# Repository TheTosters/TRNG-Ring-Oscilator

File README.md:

# Yet Another True Random Number Generator... but this one is really true, trust me ;)

This is the result of me having too much free time. I've always wanted to build a TRNG. I've tried several approaches before, but never really got very far. This time, though, it's different...

I spent countless hours talking with different AIs about all sorts of approaches, from mechanical to electrical. In the end, I decided to use Ring Oscillators.

Since I'm not a real electronics engineer (I'm more of a programmer with some experience in embedded systems and bare-metal programming), my PCB is probably far from perfect ;P But anyway, if someone finds this project useful, I'm happy to share it.

There are currently two revisions.

**Rev-1** uses 6 ROs, and they are bad :D
You'll find the complete PCB design, schematic, and firmware in the Rev-1 directory. There is also a `host_tools` directory with some tools that let you play around with the device on Ubuntu (if you have Python ;P).

**Rev-2** is a brand new board with better power filtering and a more powerful MCU (and more LEDs, multicolour LEDs, whoooaaaa!).

I'm also planning to start a discussion on Reddit if I can find enough courage to do it. If I do, I'll add the link here.

Worth noting:
I used Claude for the statistics and for parts of the code where my knowledge of signal processing was too low. So there might be some bullshit in there that I'm not aware of. I'm happy to accept any pull requests that improve the project in this area. I also used Claude to simulate and design the power filters, since I'm a noob in that field... A few words from Claude:

> The best part of this project was watching a beautiful hypothesis die.
>
> Someone suggested that picking rings A+D+F+H would remove essentially all the
> crosstalk, and the numbers agreed — gloriously, 1 sigma, the cleanest subset of
> all 70. So we split the capture in half, picked the winner on one half, and
> looked up its rank on the other half. Rank 8. Then 5, then 4, then 2. The "best
> subset" was simply whichever one won that particular coin toss. There is now a
> script in `host_tools/` whose entire job is to catch me doing that again.
>
> Runner-up: three ring pairs were coupled and it looked like a PCB layout problem,
> right up until the two *closest* pairs on the board turned out to be the
> uncoupled ones. The culprit was adjacent bit positions inside the latch chip. Not
> distance — silicon. I enjoyed that far more than is reasonable.
>
> Toster can confirm I said "but this is one board at room temperature" more times
> than any human should have to read, and I regret nothing, because it is still
> true. Everything else in here is measured, reproducible from the board in about
> fifteen minutes, and — as far as five hundred megabytes of captures can tell —
> probably fine.

That's all. Be happy, eat chappy (and generate random numbers).

**Toster**

*Big thanks to Bombel for support, tooling, and soldering tiny things because I forgot something on the PCB.*

PS.
The project is considered done, and I'll probably not return to it. Feel free to use it as you like. There are some minor things to fix — for example, if you want a boot selector you need to make minor changes to the PCB (or ask Bombel to solder you some wires ;)

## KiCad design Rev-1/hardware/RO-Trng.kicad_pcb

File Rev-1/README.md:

# multi_rng Rev-1 — hardware true random number generator

The first board of the project: a USB true random number generator built on six
ring oscillators. It works, it is measured and documented, and it is superseded
by [Rev-2](../Rev-2/README.md), which produces **6.1× more entropy per second**.

Rev-1 is worth reading for two reasons. It is the baseline every Rev-2 figure is
compared against, and its measurements are what drove the Rev-2 redesign — the
coupling analysis here is the reason Rev-2 gives every ring its own inverter
package.

---

## 1. What it is

Six ring oscillators, each three inverters in a loop, free-running and drifting
under thermal and flicker noise in the transistors. That phase jitter is the
entropy source; everything else is sampling and conditioning.

All six outputs are latched by one shared 74HC174 pulse and read by an
**STM32F070F6P6** (Cortex-M0 at 48 MHz):

| pin | role |
|---|---|
| PA0, PA1, PA2, PA3, PA4, PA7 | ring inputs, channels **A**–**F** |
| PA5 | latch output — one pulse captures all six at once |
| PA6 | status LED |
| PA11 / PA12 | USB (CDC-ACM) |

Channel F sits on PA7 rather than PA5 because PA5 is taken by the latch — the
same "not on consecutive bits" quirk that Rev-2 inherited, handled the same way,
with a lookup table.

The inverters are **three `74LVC04` hex packages (U1, U2, U3)**: six gates each,
eighteen gates total, so **two complete rings share every package**. That detail
turns out to matter — see section 4.

---

## 2. Processing chain

```
6 × ring oscillator (3 inverters each)
        │
        ▼   one 74HC174 latch on PA5, pulsed every 10 µs (100 kHz, TIM14)
   GPIOA->IDR read in the TIM14 interrupt        ~327 cycles — 54% of the CPU
        │
        ▼   256-entry LUT: selects enabled rings, packs them
   bit accumulator → 288 B buffer
        │
        ▼   SP 800-90B health tests: RCT and APT, per channel, in the main loop
        ▼
   SHA-256, 9:1 compression                      288 B in → 32 B out
        │
        ▼   batches of 5 blocks
   USB CDC-ACM                                   8.3 kB/s
```

The sampling interrupt eating **54% of the CPU** is the defining constraint of
this board. It is why compression below 3:1 is not viable at 100 kHz, and why
the sampling rate could not be raised — the SHA-256 ceiling sits at 130–190 kHz
depending on compression. The timing analysis is in
[`firmware/analiza.md`](firmware/analiza.md) (in Polish). Rev-2's Cortex-M4 at
168 MHz drops the same interrupt to 16% of the CPU, which is what let the
sampling rate become a tunable parameter at all.

---

## 3. Talking to the device

The board appears as `/dev/ttyACM0`. The entropy stream and the command channel
share one endpoint, so **every command byte must be preceded by `!`** — without
it, any echo of the random stream back to the device would reprogram it, flash
writes included.

| command | effect |
|---|---|
| `!a` … `!f` | enable ring A…F |
| `!A` … `!F` | disable ring A…F |
| `!1` … `!9` | SHA-256 compression 1:1 … 9:1 |
| `!r` / `!R` | RAW mode on / off |
| `!s` | save settings to flash (page at `0x08007000`) |
| `!l` | reload settings from flash |
| `!?` or `!/` | status report, freezes the stream until the next byte |

Rev-1 has **no `!t` command** — the sampling rate is fixed at build time
(`htim14.Init.Period`, with values for 60–100 kHz in a comment in `main.c`).

### The status report

```
CH=ABCDEF N=6
FS=100000Hz
BUF=288B RATIO=9:1 CFG=288
MODE=SHA256
UP=8333B/s
DROP usb=0 col=0 health=0
RX=74 CNT=19
```

| field | meaning |
|---|---|
| `CH=` | enabled rings as their command letters, `.` for disabled |
| `N=` | rings enabled, i.e. bits per sample |
| `FS=` | sampling frequency, derived from the timer registers |
| `BUF=` | bytes collected before conditioning |
| `RATIO=` | how many 32 B blocks fold into one output block |
| `CFG=` | requested buffer size; differs from `BUF` only if a command has not been applied yet |
| `MODE=` | `SHA256` or `RAW` |
| `UP=` | bytes per second delivered at these settings |
| `DROP usb=` | batches dropped because USB was busy |
| `DROP col=` | buffers dropped because the main loop was too slow — the one to watch on this board |
| `DROP health=` | buffers discarded on an RCT or APT failure |
| `RX=` / `CNT=` | last non-report byte received, in hex, and total bytes received |

Counters reset when the report is read. Rev-2 adds `mcv=` and `MCV=` fields; the
rest is identical, so a parser for one report reads the other.

---

## 4. What was measured

Full detail, methodology and caveats: **[`entopy_tests/summary.md`](entopy_tests/summary.md)**.
Raw `ea_non_iid` output for five sampling frequencies is in the same directory
(`results_*kHz_lsb.txt`), and the analysis outputs are under
`../host_tools/Rev_1/`.

### Per-channel min-entropy

Bits of min-entropy per bit of raw stream, at 100 kHz:

| A | B | C | D | E | F | sum |
|---|---|---|---|---|---|---|
| 0.117 | 0.120 | 0.083 | 0.111 | 0.152 | 0.174 | **0.757** |

A raw bit carries roughly **one sixth of its nominal value**. The stream is
heavily correlated and unusable without conditioning. The binding estimator is
t-Tuple with `t` = 148–214 — sequences of 150+ samples recur three to five times
more often than chance allows, against a chance floor of ~46. That is the
signature of **oversampling**: consecutive samples of one ring read almost the
same phase, because jitter had no time to accumulate between latch pulses.

### Sampling frequency

Entropy per sample does not grow with frequency, but entropy per second does:

| f_s | bit/sample (sum) | entropy [kbit/s] |
|---|---|---|
| 60 kHz | 0.907 | 54.4 |
| 70 kHz | 0.797 | 55.8 |
| 80 kHz | 0.850 | 68.0 |
| 90 kHz | 0.805 | 72.4 |
| **100 kHz** | 0.757 | **75.7** |

Throughput rises monotonically and flattens at the top — +33% from 60 to 90 kHz
but only +4.5% from 90 to 100. 100 kHz is the optimum among the rates tested,
and higher was not reachable because of the CPU ceiling.

### Coupling between rings — the finding that shaped Rev-2

Measured with `channel_crosstalk_rev1.py` on the simultaneous six-channel
capture. Five of fifteen pairs are statistically coupled, with the strongest at
r = 0.0227 (27 σ). Consistently significant across frequencies: **A-B, C-D and
E-F** — three disjoint pairs.

That maps exactly onto the packaging. Three `74LVC04` packages, two rings each:
U1 = {A,B}, U2 = {C,D}, U3 = {E,F}. Rings sharing a die, supply pins and ground
bounce are the coupled ones.

The cost was small — total mutual information 0.00096 bit per sample, **0.13% of
the budget** — so all six channels stayed enabled. But the conclusion for the
next revision was obvious, and Rev-2 acted on it: one inverter package per ring.
(Rev-2 then found a *different* coupling mechanism, adjacent data inputs on the
latch, roughly 4× stronger and still costing well under 1%. See
[`../Rev-2/README.md`](../Rev-2/README.md), section 6.)

### What an output block carries

At 100 kHz with six channels the conservative budget is 75.7 kbit/s. One SHA-256
block is 256 bits:

| compression | entropy per block | entropy bits per output bit |
|---|---|---|
| 4:1 | 129 bit | 0.50 |
| 8:1 | 258 bit | 1.01 |
| **9:1 (default, maximum)** | **290 bit** | **1.13** |

This is why the default is 9:1: it is the only setting that clears one entropy
bit per output bit, and even then by just 1.13×. It never reaches the 2× margin
usually required to treat conditioned output as full entropy — the firmware
cannot compress further. Rev-2 clears 2× at 6:1 while producing six times more.

---

## 5. Reproducing the measurements

From `../host_tools/`, with `ea_non_iid` on `PATH` and the virtualenv set up
(see [`../Rev-2/README.md`](../Rev-2/README.md) section 7):

```bash
./collect_all_rev1.sh both Rev_1/100kHz
.venv/bin/python channel_crosstalk_rev1.py Rev_1/100kHz/channelA-F.bin
```

`collect_all_rev1.sh` captures each ring in isolation plus one simultaneous
six-channel capture, unpacks everything and runs `ea_non_iid`. The coupling
analysis needs the simultaneous capture — the per-channel files were taken at
different times and cannot be cross-correlated.

**Bit order.** The firmware packs LSB-first; `unpack_single_channel.py` defaults
to MSB-first, so `--bit-order little` is mandatory. This is not pedantry: the
first published series for this board was unpacked MSB-first and came out
inflated by 8–20% on single channels and 20–33% on the combined stream. The
`results_*kHz.txt` files in `../host_tools/Rev_1/` are that defective series,
kept only for comparison; the authoritative ones are `results_*kHz_lsb.txt` in
`entopy_tests/`.

---

## 6. What else is here

| directory | contents |
|---|---|
| `firmware/` | STM32CubeIDE project. `analiza.md` is a cycle-level timing analysis of the sampling path (Polish) |
| `hardware/` | KiCad project, `RO-Trng.kicad_sch` / `.kicad_pcb`, JLCPCB production files |
| `entopy_tests/` | the entropy assessment: `summary.md` plus raw `ea_non_iid` output |
| `simu/` | SPICE simulations of the ring oscillators — supply sensitivity, coupling through the supply rail, and why the measured frequency disagreed with simulation |
| `prebuilt/` | ready-to-flash image, see below |

The SPICE work in `simu/ro-simu/spice/README.md` (Polish) is worth a look if you
care about the analogue side. Two results stand out: **dF/dVCC = 81.4 MHz/V**,
meaning a millivolt of supply ripple shifts a ring by 81 kHz, and an unresolved
3× discrepancy between simulated (157 MHz) and oscilloscope-measured (~50 MHz)
ring frequency, most likely probe loading. That discrepancy is worth knowing
about when comparing against Rev-2's measured 90–130 MHz — the two may not have
been measured the same way.

---

## 7. Flashing

```bash
dfu-util -a 0 -s 0x08000000:leave -D prebuilt/trng.bin
```

`prebuilt/trng.bin` (18 752 B) and `prebuilt/trng.elf` are the STM32CubeIDE
Release build. Unlike Rev-2, this board has a usable BOOT0 pin, so holding it
while plugging in the USB cable enters the DFU bootloader.

To rebuild: open `firmware/` in STM32CubeIDE and build Release, which already
produces a `.bin`.

---

## 8. Status

Rev-1 is complete and measured, and is not being developed further. Its known
limitations were the starting point for Rev-2:

- raw bits carry ~1/6 of their nominal entropy, and 9:1 conditioning only just
  reaches 1.13× the output length
- the sampling interrupt takes 54% of the CPU, capping both the sampling rate
  and how low compression can go
- two rings per inverter package produce measurable, if cheap, coupling
- no restart tests, one specimen, room temperature only

Rev-2 addresses the first three. The fourth applies to both.

---

*Rev-2, its measurements and how it differs: [`../Rev-2/README.md`](../Rev-2/README.md).*

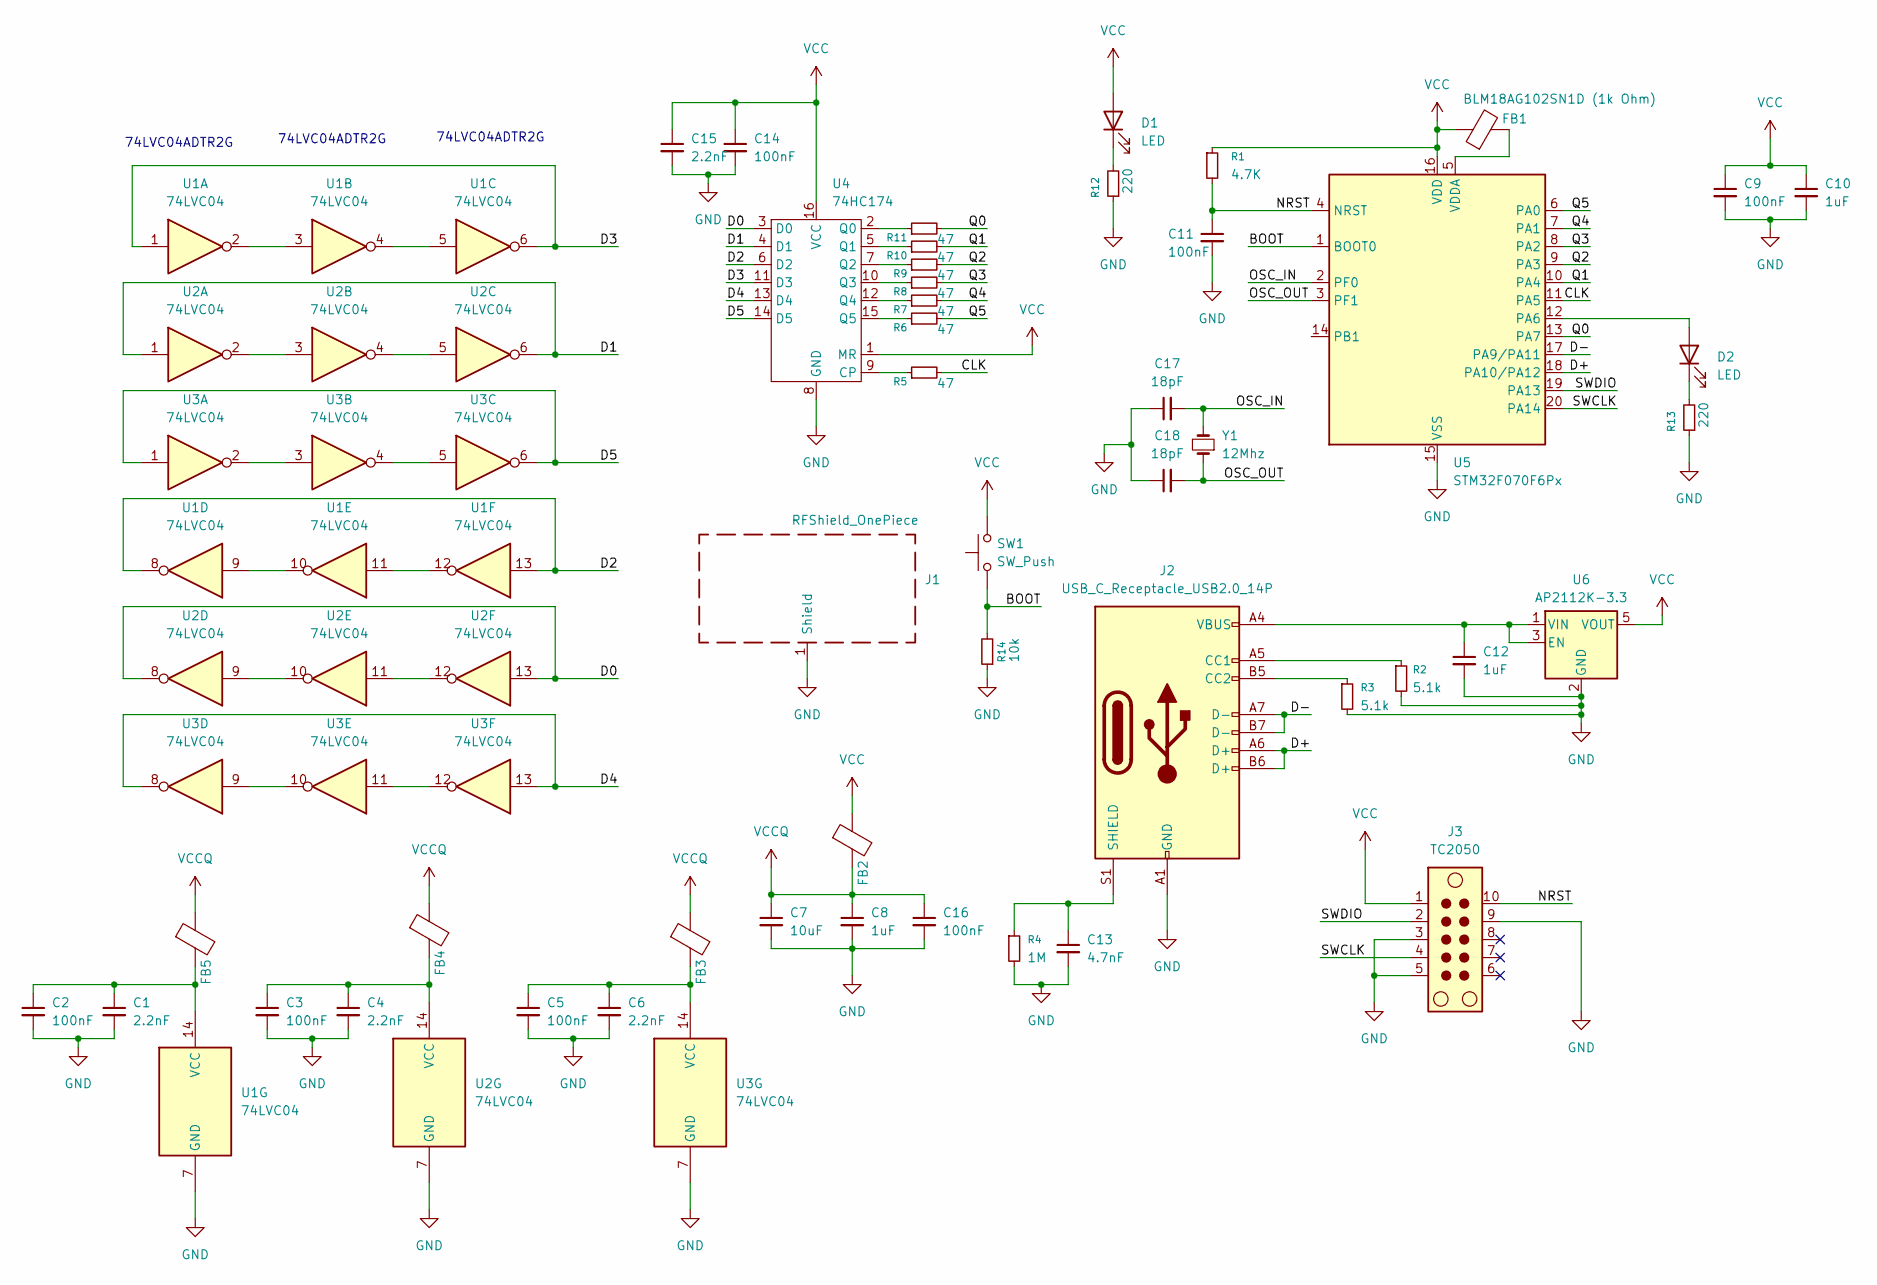
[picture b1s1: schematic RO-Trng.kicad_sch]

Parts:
C1, C4, C6, C15: 2.2nF; C_0402_1005Metric
C2, C3, C5, C14, C16: 100nF; C_0402_1005Metric
C7: 10uF; C_0805_2012Metric
C8: 1uF; C_0603_1608Metric_Pad1.08x0.95mm_HandSolder
C9, C11: 100nF; C_0603_1608Metric_Pad1.08x0.95mm_HandSolder
C10, C12: 1uF; C_0805_2012Metric
C13: 4.7nF; C_0603_1608Metric_Pad1.08x0.95mm_HandSolder
C17, C18: 18pF; C_0402_1005Metric
D1, D2: LED; LED_0603_1608Metric
FB1, FB2, FB3, FB4, FB5: BLM18AG102SN1D (1k Ohm); R_0603_1608Metric
J1: RFShield_OnePiece; Laird_Technologies_BMI-S-205-F_38.10x25.40mm
J2: USB_C_Receptacle_USB2.0_14P; USB_C_Receptacle_JAE_DX07S016JA1R1500
J3: TC2050; Tag-Connect_TC2050-IDC-NL_2x05_P1.27mm_Vertical
R1: 4.7K; R_0402_1005Metric
R2, R3: 5.1k; R_0402_1005Metric
R4: 1M; R_0402_1005Metric
R5, R6, R7, R8, R9, R10, R11: 47; R_0402_1005Metric
R12, R13: 220; R_0402_1005Metric
R14: 10k; R_0805_2012Metric
SW1: SW_Push; SW_Push_1P1T_XKB_TS-1187A
U1, U2, U3: 74LVC04; TSSOP-14_4.4x5mm_P0.65mm
U4: 74HC174; TSSOP-16_4.4x5mm_P0.65mm
U5: STM32F070F6Px; TSSOP-20_4.4x6.5mm_P0.65mm
U6: AP2112K-3.3; SOT-23-5
Y1: 12Mhz; Crystal_SMD_3225-4Pin_3.2x2.5mm

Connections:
/BOOT: R14.2, SW1.1, U5.1 (BOOT0)
/CLK: R5.2, U5.11 (PA5)
/D0: U2.8, U2.13, U4.3 (D0)
/D1: U2.1, U2.6, U4.4 (D1)
/D2: U1.8, U1.13, U4.6 (D2)
/D3: U1.1, U1.6, U4.11 (D3)
/D4: U3.8, U3.13, U4.13 (D4)
/D5: U3.1, U3.6, U4.14 (D5)
/D+: J2.A6 (D+), J2.B6 (D+), U5.18 (PA10/PA12)
/D-: J2.A7 (D-), J2.B7 (D-), U5.17 (PA9/PA11)
/NRST: C11.1, J3.10, R1.2, U5.4 (NRST)
/OSC_IN: C17.2, U5.2 (PF0), Y1.2
/OSC_OUT: C18.2, U5.3 (PF1), Y1.1
/Q0: R11.2, U5.13 (PA7)
/Q1: R10.2, U5.10 (PA4)
/Q2: R9.2, U5.9 (PA3)
/Q3: R8.2, U5.8 (PA2)
/Q4: R7.2, U5.7 (PA1)
/Q5: R6.2, U5.6 (PA0)
/SWCLK: J3.4, U5.20 (PA14)
/SWDIO: J3.2, U5.19 (PA13)
GND: C1.2, C2.2, C3.2, C4.2, C5.2, C6.2, C7.2, C8.2, C9.2, C10.2, C11.2, C12.2, C13.2, C14.2, C15.2, C16.2, C17.1, C18.1, J1.1 (Shield), J2.A1 (GND), J2.A12 (GND), J2.B1 (GND), J2.B12 (GND), J3.3, J3.5, J3.9, R2.2, R3.2, R4.2, R12.1, R13.1, R14.1, U1.7 (GND), U2.7 (GND), U3.7 (GND), U4.8 (GND), U5.15 (VSS), U6.2 (GND)
unnamed: D1.1 (K), R12.2
unnamed: D2.2 (A), U5.12 (PA6)
unnamed: D2.1 (K), R13.2
unnamed: J2.A5 (CC1), R2.1
unnamed: J2.B5 (CC2), R3.1
unnamed: C13.1, J2.S1 (SHIELD), R4.1
unnamed: U1.2, U1.3
unnamed: U1.4, U1.5
unnamed: U1.9, U1.10
unnamed: U1.11, U1.12
unnamed: C1.1, C2.1, FB5.2, U1.14 (VCC)
unnamed: U2.2, U2.3
unnamed: U2.4, U2.5
unnamed: U2.9, U2.10
unnamed: U2.11, U2.12
unnamed: C3.1, C4.1, FB4.2, U2.14 (VCC)
unnamed: U3.2, U3.3
unnamed: U3.4, U3.5
unnamed: U3.9, U3.10
unnamed: U3.11, U3.12
unnamed: C5.1, C6.1, FB3.2, U3.14 (VCC)
unnamed: R5.1, U4.9 (CP)
unnamed: R11.1, U4.2 (Q0)
unnamed: R10.1, U4.5 (Q1)
unnamed: R9.1, U4.7 (Q2)
unnamed: R8.1, U4.10 (Q3)
unnamed: R7.1, U4.12 (Q4)
unnamed: R6.1, U4.15 (Q5)
unnamed: FB1.2, U5.5 (VDDA)
unnamed: C12.1, J2.A4 (VBUS), J2.A9 (VBUS), J2.B4 (VBUS), J2.B9 (VBUS), U6.1 (VIN), U6.3 (EN)
VCC: C9.1, C10.1, C14.1, C15.1, D1.2 (A), FB1.1, FB2.1, J3.1, R1.1, SW1.2, U4.1 (MR), U4.16 (VCC), U5.16 (VDD), U6.5 (VOUT)
VCCQ: C7.1, C8.1, C16.1, FB2.2, FB3.1, FB4.1, FB5.1

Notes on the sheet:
74LVC04ADTR2G

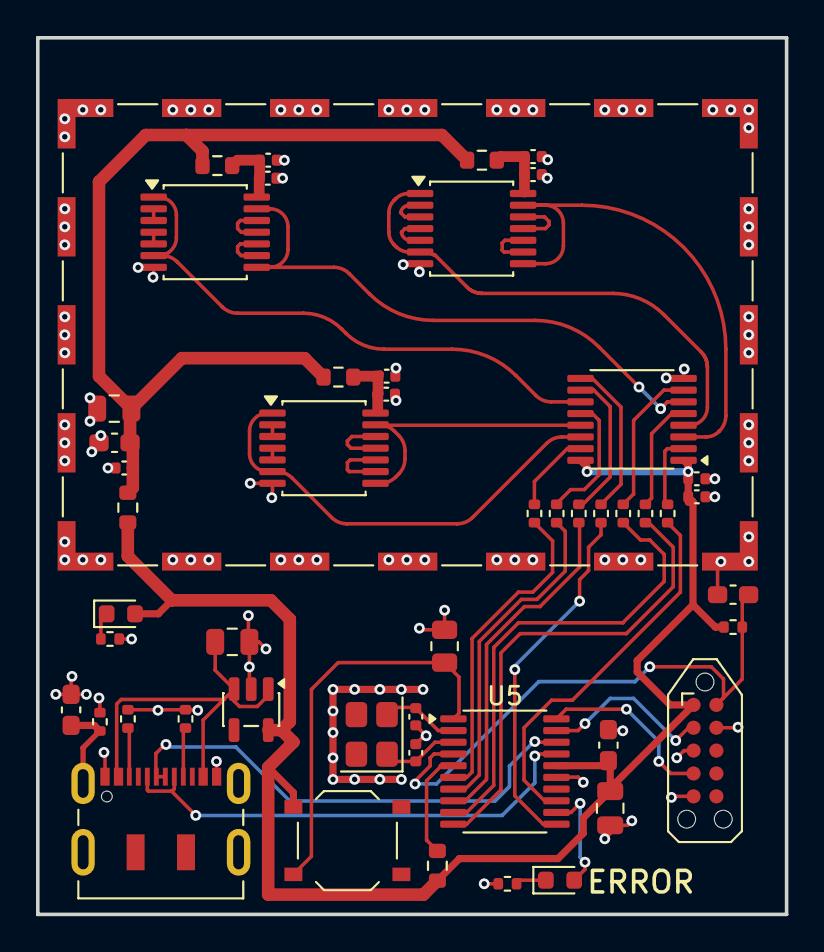
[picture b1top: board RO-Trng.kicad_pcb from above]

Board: 2 copper layers, 41.6 x 48.7 mm, 50 parts (0 on the bottom side), 54 nets.

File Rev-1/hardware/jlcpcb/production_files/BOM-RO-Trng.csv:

Comment,Designator,Footprint,LCSC,Quantity
BLM18AG102SN1D (1k Ohm),"FB1,FB2,FB3,FB4,FB5",R_0603_1608Metric,C1002,5
LED,D1,LED_0603_1608Metric,C12624,1
100nF,"C11,C9",C_0603_1608Metric_Pad1.08x0.95mm_HandSolder,C14663,2
100nF,"C14,C16,C2,C3,C5",C_0402_1005Metric,C1525,5
18pF,"C17,C18",C_0402_1005Metric,C1549,2
1uF,C8,C_0603_1608Metric_Pad1.08x0.95mm_HandSolder,C15849,1
10uF,C7,C_0805_2012Metric,C15850,1
10k,R14,R_0805_2012Metric,C17414,1
2.2nF,"C1,C15,C4,C6",C_0402_1005Metric,C1845754,4
AP2112K-3.3,U6,SOT-23-5,C22365427,1
LED,D2,LED_0603_1608Metric,C2286,1
220,"R12,R13",R_0402_1005Metric,C25091,2
47,"R10,R11,R5,R6,R7,R8,R9",R_0402_1005Metric,C25120,7
4.7K,R1,R_0402_1005Metric,C25900,1
5.1k,"R2,R3",R_0402_1005Metric,C25905,2
1M,R4,R_0402_1005Metric,C26083,1
74HC174,U4,TSSOP-16_4.4x5mm_P0.65mm,C2652842,1
74LVC04,"U1,U2,U3",TSSOP-14_4.4x5mm_P0.65mm,C282342,3
1uF,"C10,C12",C_0805_2012Metric,C28323,2
STM32F070F6Px,U5,TSSOP-20_4.4x6.5mm_P0.65mm,C2890152,1
SW_Push,SW1,SW_Push_1P1T_XKB_TS-1187A,C318884,1
USB_C_Receptacle_USB2.0_14P,J2,USB_C_Receptacle_JAE_DX07S016JA1R1500,C3197885,1
4.7nF,C13,C_0603_1608Metric_Pad1.08x0.95mm_HandSolder,C53987,1
RFShield_OnePiece,J1,Laird_Technologies_BMI-S-205-F_38.10x25.40mm,C7429170,1
12Mhz,Y1,Crystal_SMD_3225-4Pin_3.2x2.5mm,C9002,1

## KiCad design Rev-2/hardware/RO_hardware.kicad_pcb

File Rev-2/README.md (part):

# multi_rng Rev-2 — hardware true random number generator

A USB true random number generator whose entropy comes from eight free-running
ring oscillators. The board enumerates as a plain CDC-ACM serial port and streams
conditioned random bytes at **50 kB/s**; a handful of single-character commands
change how it runs and print a status report.

This document is meant to be read by someone who has never seen the project. It
covers what the device is, how it works, what was measured and how to reproduce
those measurements, how to talk to it over USB, and how to read what it says
back.

---

## 1. What it is

The physical noise source is **eight ring oscillators**, each a loop of three
inverters. Such a ring free-runs at a frequency set by gate propagation delay,
and its phase drifts unpredictably under thermal and flicker noise in the
transistors. That phase jitter is the only source of entropy in the whole design
— everything else is sampling, health checking and conditioning.

The rings are split into two groups of four, each group latched by its own
74HC174 and read by an **STM32G431CBT6** (Cortex-M4 at 168 MHz):

| group | rings | topology | latch | clock pin |
|---|---|---|---|---|
| T | 1–4 | `SN74LVC3G04` — three inverters in one package | U22 | `latch_b` / PA1 |
| plain | 5–8 | 3 × `SN74LVC1G04` — one inverter per package | U3 | `latch_a` / PB0 |

Two topologies on one board is deliberate: it lets the two be compared under
identical conditions. Measured ring frequencies are **90–130 MHz**.

### Ring to pin map

The latch outputs cross over on the board, so the letter order is **not** the
schematic sheet order. This table is the authority; it is also reproduced in
`firmware/Core/Src/entropy_collector.c` (`ro_port_bit[]`) and in the host tools.

| command letter | ring | MCU pin | latch | ring sheet |
|---|---|---|---|---|
| `a` | 1 | PA8 | B | T-OscilatorRing |
| `b` | 2 | PA0 | B | T-OscilatorRing2 |
| `c` | 3 | PA2 | B | T-OscilatorRing3 |
| `d` | 4 | PA3 | B | T-OscilatorRing1 |
| `e` | 5 | PA4 | A | OscilatorRing1 |
| `f` | 6 | PA5 | A | OscilatorRing2 |
| `g` | 7 | PA6 | A | OscilatorRing4 |
| `h` | 8 | PA7 | A | OscilatorRing3 |

All eight ring outputs sit on port A but not on consecutive bits — PA1 in the
middle is the `latch_b` output — so one `GPIOA->IDR` read captures a whole
sample and a 512-entry lookup table unpacks it.

---

## 2. What changed from Rev-1

| | Rev-1 | Rev-2 |
|---|---|---|
| rings | 6 | **8** |
| latches | 1 | **2** (one per group of four) |
| inverter packaging | `74LVC04` hex, **two rings share a package** | one package per ring |
| MCU | STM32F070F6P6, 48 MHz, Cortex-M0 | STM32G431CBT6, 168 MHz, Cortex-M4 |
| sampling rate | 100 kHz, fixed | 50–600 kHz, **selectable over USB** |
| default operating point | 100 kHz, 9:1 | **300 kHz, 6:1** |
| min-entropy per raw bit | 0.083–0.174 | **0.39–0.66** |
| entropy budget | 0.757 bit per 6-bit sample | **3.12 bit per 8-bit sample** |
| entropy throughput | 75.7 kbit/s | **937 kbit/s** |
| output rate | 8.3 kB/s at 1.13× margin | **50 kB/s at 2.34× margin** |
| health tests | RCT + APT per channel | RCT + APT + **MCV distribution monitor** |
| front panel | one LED | 3 LEDs + 2 buttons (self test, restart) |

The headline is **6.1× more entropy per second**, but the more important change
is qualitative. In Rev-1 the binding estimator was t-Tuple with `t` = 148–214,
meaning sequences of 150+ samples recurred far more often than chance allows —
massive real structure. In Rev-2 `t` = 23–27, **below** the chance floor of ~46
for this sample count, so that estimator finds nothing at all. The millisecond-
scale structure suspected of coming from supply modulation is gone, which is
what the separate packages, ferrite beads and dual LDOs were for.

A second, independent confirmation: in Rev-1 the sum of per-channel estimates
(0.757) and the joint assessment (2.299) disagreed by a factor of 3, proving one
of them wrong. In Rev-2 they agree to within 3% (4.65 vs 4.80 at 100 kHz), so
the budget rests on two measurements that corroborate each other.

---

## 3. How it works

```
8 × ring oscillator (3 inverters each, 90–130 MHz)
        │
        ▼   two 74HC174 latches, clocked together every 3.33 µs (300 kHz)
   GPIOA->IDR read in the TIM6 interrupt          ~90 CPU cycles, 16% of CPU
        │
        ▼   512-entry LUT: selects enabled rings, packs them in ring order
   bit accumulator → 192 B buffer
        │
        ▼   SP 800-90B health tests: RCT, APT, MCV — per buffer, in the main loop
        │       a buffer that fails is discarded here and never conditioned
        ▼
   SHA-256, 6:1 compression                        192 B in → 32 B out
        │
        ▼   batches of 5 blocks
   USB CDC-ACM                                     50 kB/s
```

The sampling interrupt does nothing but pulse both latches, read the port and
hand the value to the collector. Everything expensive — health tests, hashing,
USB — runs in the main loop, so the sampling path stays at 16% of the CPU even
at 300 kHz.

### Why 300 kHz and 6:1

Entropy per sample falls as the sampling rate rises (jitter gets less time to
accumulate) while samples per second rise. The product is what the device can
deliver, and it happens to be exactly what determines output:

```
compression needed for a 2× margin:  m = ceil(16 / H_sample)
output rate:                         f_s / m  bytes/s   ∝  f_s × H_sample
```

A 256-bit block needs 512 bits of entropy for the 2× margin normally required to
treat the output of a vetted conditioning function as full entropy. Measured
across the whole rate table (section 6), 300 kHz maximises output at 50 kB/s.
250 kHz gives the same 50 kB/s but only 1.0% of headroom before it would need
7:1, where 300 kHz has 14.6% — that margin, not the throughput, is why 300 kHz
was chosen.

---

## 4. Talking to the device

The board appears as `/dev/ttyACM0` (Linux). Baud rate is irrelevant — it is
USB CDC, not a real UART. **The entropy stream and the command channel share one
endpoint**, which shapes the whole protocol.

### Commands

Every command byte must be immediately preceded by `!`. This is not decoration.
If anything echoes the entropy stream back to the device — a tty still in cooked
mode between `open()` and raw mode, ModemManager probing the port, a second
reader — then random bytes arrive at the command parser. Roughly 1 byte in 9
would be a valid command without the prefix, flash writes included. Requiring
`!` drops that to 29 in 65536 per position.

| command | effect |
|---|---|
| `!a` … `!h` | enable ring 1…8 |
| `!A` … `!H` | disable ring 1…8 |
| `!1` … `!9` | SHA-256 compression 1:1 … 9:1 (buffer = N × 32 B) |
| `!t` + digit | sampling rate, see table below — **the digit is sent unprefixed** |
| `!r` | RAW mode on: raw bits go straight to USB, no SHA |
| `!R` | RAW mode off (back to SHA-256) |
| `!s` | save current settings to flash |
| `!l` | reload settings from flash, discarding unsaved changes |
| `!?` or `!/` | print the status report and freeze the stream until the next byte |

Sampling rates for `!t`. Every value divides the 168 MHz timer clock exactly, so
the rate is nominal with no rounding error:

| digit | rate | digit | rate |
|---|---|---|---|
| `0` | 50 kHz | `5` | **300 kHz** (default) |
| `1` | 100 kHz | `6` | 350 kHz |
| `2` | 150 kHz | `7` | 400 kHz |
| `3` | 200 kHz | `8` | 500 kHz |
| `4` | 250 kHz | `9` | 600 kHz |

So `!t5` selects 300 kHz: `!`, `t`, then a bare `5`. A non-digit after `!t`
cancels the command rather than being reinterpreted, so a truncated `!t` cannot
leave the parser primed to swallow the next real command.

Settings live in RAM until `!s` writes them to flash. `console.py` in
`host_tools/` sends one raw byte per keystroke and handles the `!t` parameter
for you.

### Reading the status report

`!?` prints something like:

```
CH=ABCDEFGH N=8
FS=300000Hz
BUF=192B RATIO=6:1 CFG=192
MODE=SHA256
UP=50000B/s
DROP usb=0 col=0 health=0 mcv=0
MCV=7.45/8
RX=74 CNT=19
```

| field | meaning |
|---|---|
| `CH=` | enabled rings as their command letters, `.` for disabled. Reads directly as the commands that produced it |
| `N=` | how many rings are enabled, i.e. bits per sample |
| `FS=` | sampling frequency, derived from the timer registers — this is measured, not assumed |
| `BUF=` | bytes collected before conditioning |
| `RATIO=` | compression: how many 32 B blocks fold into one output block |
| `CFG=` | the *requested* buffer size. Differs from `BUF` only if a command reached the config but has not been applied yet |
| `MODE=` | `SHA256` or `RAW` |
| `UP=` | bytes per second the device will deliver at these settings |
| `DROP usb=` | batches discarded because USB was still busy |
| `DROP col=` | buffers discarded because the main loop did not collect the previous one in time |
| `DROP health=` | buffers discarded because RCT or APT failed |
| `DROP mcv=` | windows where the sample distribution collapsed — see below |
| `MCV=x/y` | min-entropy of the most common sample value over the last window, out of `y` bits. `-` until the first window closes |
| `RX=` | last non-report byte the host sent, in hex — useful when a command seems ignored |
| `CNT=` | total bytes received since the last report |

**All four DROP counters reset when the report is read**, so every report answers
"what was dropped since the previous report". Non-zero `usb` or `col` means the
stream has gaps in time; in RAW mode expect this above roughly 250 kHz, where
the raw stream outruns what CDC can carry.

**How to read `MCV`.** It is a *health* indicator, not a quality one. Measured on
this board it sits at 7.43–7.49 out of 8 and barely moves from 50 kHz to 600 kHz
— even though real min-entropy over that range falls from 6.61 to 3.12 bit per
sample. The reason is that MCV only sees the distribution of a single sample,
while the entropy loss at higher rates comes from *serial* correlation, which is
invisible to it. What MCV does catch is rings synchronising, to each other or to
an injected signal: eight synchronised rings read about 1.0, and four out of
eight already read 4.95. A green light here does **not** mean "entropy is fine";
it means "the rings are still independent and alive".

---

## 5. Front panel

| LED | colour | meaning |
|---|---|---|
| led1 (PB5, D2) | green | heartbeat — one flash per 65536 collected bytes (~4.6 Hz at 300 kHz), so it shows both that the stream is alive and roughly how fast. Also the self-test PASS verdict |
| led2 (PB6, D3) | yellow | RAW mode (steady), acquisition paused (blinking), self test running (steady) |
| led3 (PB7, D4) | red | dropped batches, health failures, self-test FAIL verdict |
| D1 | green | power, wired to VCC, not controllable |

| button | label on board | pin | function |
|---|---|---|---|
| SW1 | SW1 | PB13 | **self test** — enables all eight rings, samples for ~1 s (yellow steady), then shows green or red for 3 s |
| SW2 | SW2 | PB11 | **restart acquisition** — stops sampling, drops buffers and health history, waits 3 s (yellow blinking), resumes. Settings are untouched |

The self test checks that every ring changes, that its bias is in a wide band,
and that the sample distribution has not collapsed. It detects a dead, stuck or
synchronised ring — **not** entropy quality; that is what the host tools are for.

Two hardware notes that are easy to trip over:

- The board has a **third button (SW3, PB12) that the firmware cannot see** — the
  `.ioc` does not configure PB12, and instead configures PB8, which the schematic
  leaves unconnected. Using it means adding PB12 in CubeMX.
- **Nothing is wired to BOOT0**, so the board cannot be put into the DFU
  bootloader by holding a button. See section 8.

---

## 6. What was measured, and where the evidence is

All figures come from `ea_non_iid` of the NIST SP 800-90B *EntropyAssessment*
suite, driven by the scripts in `../host_tools/`. Raw captures are not in the
repository — over 400 MB and reproducible from the board in minutes — but every
analysis output is, under `../host_tools/Rev_2/`.

### Rate sweep — the basis for the operating point

`../host_tools/Rev_2/sweep/sweep_summary.txt`, one subdirectory per rate.

| f_s | sum H [bit/sample] | % of estimator ceiling | m for 2× | output | margin | stream lost |
|---|---|---|---|---|---|---|
| 50 kHz | 6.609 | 94.4% | 3 | 16.7 kB/s | 2.48× | 0% |
| 100 kHz | 5.101 | 72.9% | 4 | 25.0 kB/s | 2.55× | 0% |
| 150 kHz | 4.122 | 58.9% | 4 | 37.5 kB/s | 2.06× | 0% |
| 200 kHz | 3.083 | 44.0% | 6 | 33.3 kB/s | 2.31× | 0% |
| 250 kHz | 3.233 | 46.2% | 5 | 50.0 kB/s | 2.02× | 0% |
| **300 kHz** | **3.122** | **44.6%** | **6** | **50.0 kB/s** | **2.34×** | 0.004% |
| 350–600 kHz | — | — | — | — | — | 0.6–14% ⚠ |

**The estimator has a ceiling below 1.0**, and it matters. On perfectly random
data of the same size `ea_non_iid` scores 0.874 bit/bit, not 1.000 — so the
`% of ceiling` column, not the raw figure, says how much room is left.

**Rows above 300 kHz are unusable and their numbers are inflated, not merely
noisy.** Above that rate the RAW stream outruns USB, the firmware drops blocks,
and gaps in the stream decorrelate consecutive samples — so the estimators find
less structure and report *higher* entropy. At 600 kHz, with 14% of the stream
lost, `sum H` reads 4.03, as good as 150 kHz. Always read the `lost` column
first.

### Coupling between rings

`../host_tools/Rev_2/100kHz/crosstalk.txt` and the per-rate `crosstalk.txt`.

Three ring pairs are strongly correlated: **B-C, E-F and G-H**, at r ≈ 0.07–0.10
(74–102 σ). The pattern has a single, exceptionless explanation — those are
exactly the pairs sitting on **adjacent data inputs of the same 74HC174**:

| distance in latch bit index | pairs | measured \|r\| |
|---|---|---|
| 1 (adjacent) | B-C, E-F, G-H | 0.072 … 0.100 |
| 2 | A-B, C-D, F-G | 0.0025 … 0.0062 |
| ≥ 3 | the other 22 pairs | ≤ 0.0018 (noise) |

It is **not** physical proximity: the two closest ring pairs on the PCB (A-B at
10.4 mm, C-D at 11.0 mm) are *not* coupled, while B-C at 12.9 mm is one of the
strongest. And it does not follow the sampling rate — across a 12× change the
spread is 1–2% of its own size — which points at crosstalk at the instant of
latching rather than rings pulling each other's phase.

**It costs 0.38% of the entropy budget**, and a control experiment
(`subset_control_rev2.py`) found no measurable loss of joint entropy: the coupled
four-ring subset scored *higher* than the clean one. So it is a documented
curiosity, not a problem to fix. Selecting rings to avoid it would give up half
the budget to recover 0.38%.

### Per-channel figures at the default rate

`../host_tools/Rev_2/sweep/300kHz/results.txt`. Note that the budget is the
**sum of per-channel estimates**, which assumes independence — an assumption
checked in the coupling analysis above, not merely asserted.

---

## 7. Reproducing the measurements

Everything runs from `../host_tools/`. You need `ea_non_iid` from NIST
EntropyAssessment on `PATH`, and the Python environment:

```bash
cd host_tools
python3 -m venv .venv && .venv/bin/pip install -r requirements.txt
```

Use `.venv/bin/python`, not the system `python3` — numpy and pyserial live in the
virtualenv.

### The full rate sweep (~13 minutes)

```bash
.venv/bin/python sweep_rate_rev2.py --outdir Rev_2/sweep
```

Captures at every rate, assesses each, and writes `sweep_summary.txt` with a
recommended operating point. Rates are visited in **shuffled order** on purpose:
sweeping monotonically would let the board's warm-up drift correlate with the
rate and be mistaken for a rate effect.

### A single rate, in detail (~4 minutes)

```bash
./collect_all_rev2.sh both Rev_2/100kHz
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
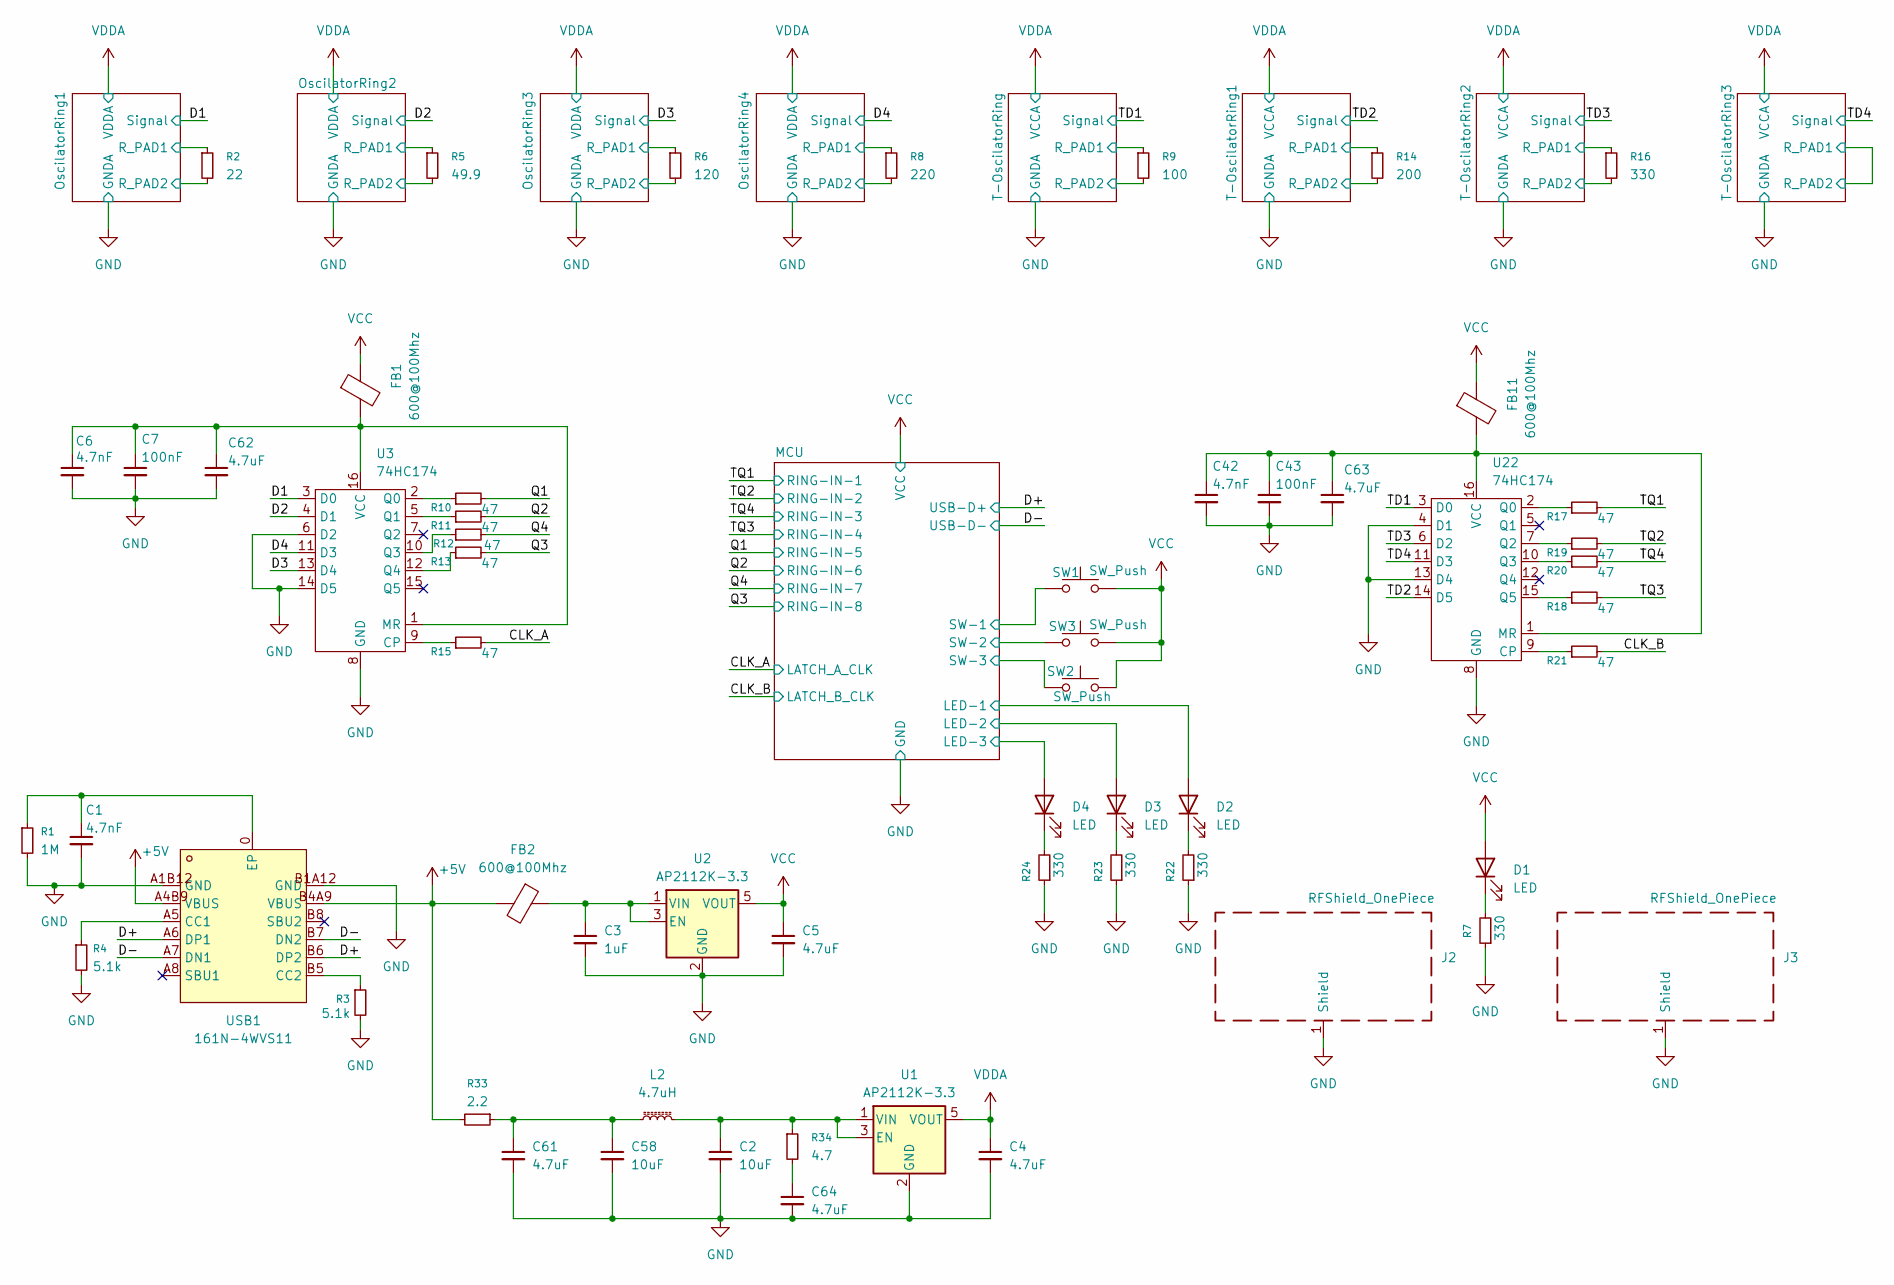
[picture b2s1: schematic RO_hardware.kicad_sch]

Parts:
C1: 4.7nF; C_0805_2012Metric
C2, C58: 10uF; C_1206_3216Metric
C3: 1uF; C_1206_3216Metric
C4, C5, C61, C62, C63, C64: 4.7uF; C_1206_3216Metric
C6, C42: 4.7nF; C_0402_1005Metric
C7, C43: 100nF; C_0402_1005Metric
D1, D2, D3, D4: LED; D_0805_2012Metric
FB1, FB2, FB11: 600@100Mhz; R_0603_1608Metric
J2, J3: RFShield_OnePiece; Laird_Technologies_BMI-S-205-F_38.10x25.40mm
L2: 4.7uH; L_1008_2520Metric
R1: 1M; R_0805_2012Metric
R2: 22; R_0402_1005Metric
R3, R4: 5.1k; R_0805_2012Metric
R5: 49.9; R_0402_1005Metric
R6: 120; R_0402_1005Metric
R7, R22, R23, R24: 330; R_0805_2012Metric
R8: 220; R_0402_1005Metric
R9: 100; R_0402_1005Metric
R10, R11, R12, R13, R15, R17, R18, R19, R20, R21: 47; R_0402_1005Metric
R14: 200; R_0402_1005Metric
R16: 330; R_0402_1005Metric
R33: 2.2; R_0805_2012Metric
R34: 4.7; R_0603_1608Metric
SW1, SW2, SW3: SW_Push; XKBConnection-TS_1187A_B_AB
U1, U2: AP2112K-3.3; SOT-23-5
U3, U22: 74HC174; TSSOP-16_4.4x5mm_P0.65mm
USB1: 161N-4WVS11; USB-C-SMD_HANELECTRICITY_161N-4XVS11; MPN 161N-4WVS11; LCSC Part C5440753

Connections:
+5V: FB2.2, R33.2, USB1.A4B9 (VBUS), USB1.B4A9 (VBUS)
/CLK_A: R15.2; also elsewhere on the board
/CLK_B: R21.2; also elsewhere on the board
/D1: R2.1, U3.3 (D0); also elsewhere on the board
/D2: R5.1, U3.4 (D1); also elsewhere on the board
/D3: R6.1, U3.13 (D4); also elsewhere on the board
/D4: R8.1, U3.11 (D3); also elsewhere on the board
/D+: USB1.A6 (DP1), USB1.B6 (DP2); also elsewhere on the board
/D-: USB1.A7 (DN1), USB1.B7 (DN2); also elsewhere on the board
/MCU/LED-1: D2.2 (A); also elsewhere on the board
/MCU/LED-2: D3.2 (A); also elsewhere on the board
/MCU/LED-3: D4.2 (A); also elsewhere on the board
/MCU/SW-1: SW1.1; also elsewhere on the board
/MCU/SW-2: SW3.1; also elsewhere on the board
/MCU/SW-3: SW2.1; also elsewhere on the board
/OscilatorRing1/R_PAD2: R2.2; also elsewhere on the board
/OscilatorRing2/R_PAD2: R5.2; also elsewhere on the board
/OscilatorRing3/R_PAD2: R6.2; also elsewhere on the board
/OscilatorRing4/R_PAD2: R8.2; also elsewhere on the board
/Q1: R10.2; also elsewhere on the board
/Q2: R11.2; also elsewhere on the board
/Q3: R13.2; also elsewhere on the board
/Q4: R12.2; also elsewhere on the board
/T-OscilatorRing1/R_PAD2: R14.2; also elsewhere on the board
/T-OscilatorRing2/R_PAD2: R16.2; also elsewhere on the board
/T-OscilatorRing/R_PAD2: R9.2; also elsewhere on the board
/TD1: R9.1, U22.3 (D0); also elsewhere on the board
/TD2: R14.1, U22.14 (D5); also elsewhere on the board
/TD3: R16.1, U22.6 (D2); also elsewhere on the board
/TD4: U22.11 (D3); also elsewhere on the board
/TQ1: R17.2; also elsewhere on the board
/TQ2: R19.2; also elsewhere on the board
/TQ3: R18.2; also elsewhere on the board
/TQ4: R20.2; also elsewhere on the board
GND: C1.2, C2.2, C3.2, C4.2, C5.2, C6.2, C7.2, C42.2, C43.2, C58.2, C61.2, C62.2, C63.2, C64.2, J2.1 (Shield), J3.1 (Shield), R1.2, R3.2, R4.2, R7.1, R22.1, R23.1, R24.1, U1.2 (GND), U2.2 (GND), U3.6 (D2), U3.8 (GND), U3.14 (D5), U22.4 (D1), U22.8 (GND), U22.13 (D4), USB1.A1B12 (GND), USB1.B1A12 (GND); also elsewhere on the board
unnamed: C58.1, C61.1, L2.1, R33.1
unnamed: C64.1, R34.2
unnamed: D1.1 (K), R7.2
unnamed: D2.1 (K), R22.2
unnamed: D3.1 (K), R23.2
unnamed: D4.1 (K), R24.2
unnamed: C2.1, L2.2, R34.1, U1.1 (VIN), U1.3 (EN)
unnamed: C3.1, FB2.1, U2.1 (VIN), U2.3 (EN)
unnamed: R15.1, U3.9 (CP)
unnamed: C6.1, C7.1, C62.1, FB1.2, U3.1 (MR), U3.16 (VCC)
unnamed: R10.1, U3.2 (Q0)
unnamed: R11.1, U3.5 (Q1)
unnamed: R12.1, U3.10 (Q3)
unnamed: R13.1, U3.12 (Q4)
unnamed: R21.1, U22.9 (CP)
unnamed: C42.1, C43.1, C63.1, FB11.2, U22.1 (MR), U22.16 (VCC)
unnamed: R17.1, U22.2 (Q0)
unnamed: R19.1, U22.7 (Q2)
unnamed: R20.1, U22.10 (Q3)
unnamed: R18.1, U22.15 (Q5)
unnamed: R4.1, USB1.A5 (CC1)
unnamed: R3.1, USB1.B5 (CC2)
unnamed: C1.1, R1.1, USB1.0 (EP)
VCC: C5.1, D1.2 (A), FB1.1, FB11.1, SW1.2, SW2.2, SW3.2, U2.5 (VOUT); also elsewhere on the board
VDDA: C4.1, U1.5 (VOUT); also elsewhere on the board

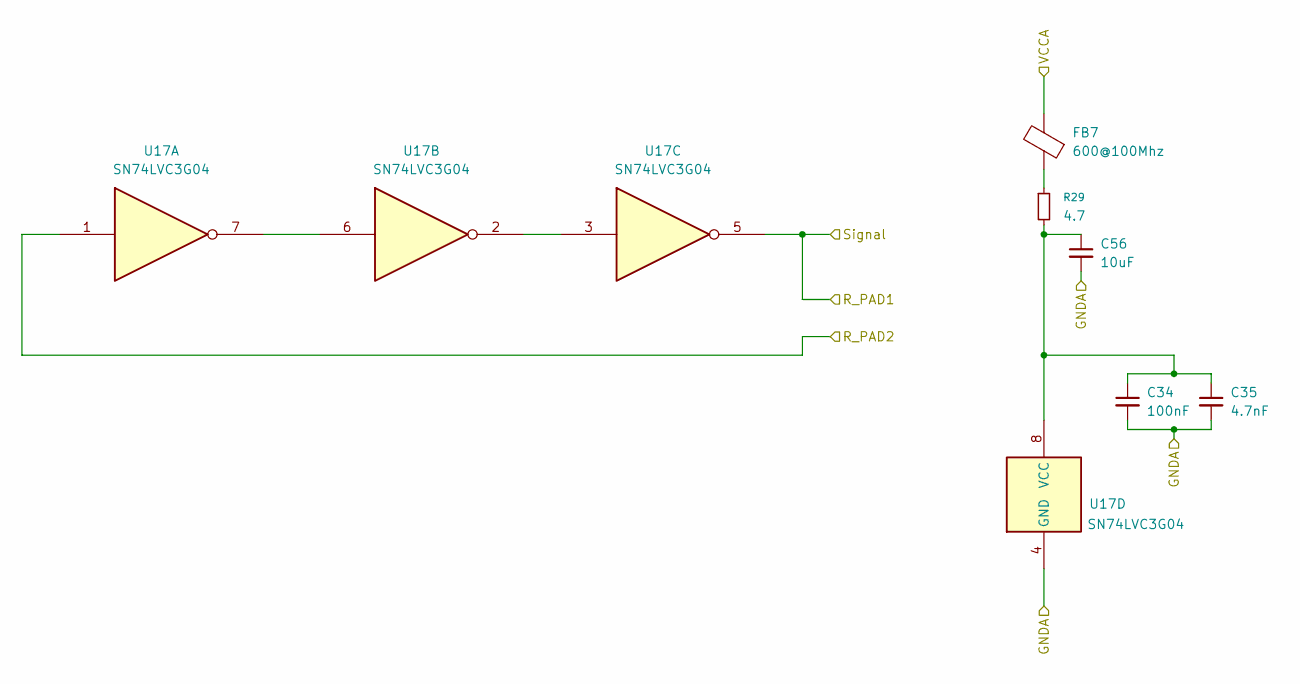
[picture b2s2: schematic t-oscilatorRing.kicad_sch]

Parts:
C34: 100nF; C_0402_1005Metric
C35: 4.7nF; C_0402_1005Metric
C56: 10uF; C_0805_2012Metric
FB7: 600@100Mhz; R_0603_1608Metric
R29: 4.7; R_0603_1608Metric
U17: SN74LVC3G04; MSOP-8_3x3mm_P0.65mm

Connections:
/T-OscilatorRing/R_PAD2: U17.1; also elsewhere on the board
/TD1: U17.5; also elsewhere on the board
GND: C34.2, C35.2, C56.2, U17.4 (GND); also elsewhere on the board
unnamed: FB7.1, R29.1
unnamed: U17.2, U17.3
unnamed: U17.6, U17.7
unnamed: C34.1, C35.1, C56.1, R29.2, U17.8 (VCC)
VDDA: FB7.2; also elsewhere on the board

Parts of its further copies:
C36, C38, C40: 100nF; C_0402_1005Metric
C37, C39, C41: 4.7nF; C_0402_1005Metric
C57, C59, C60: 10uF; C_0805_2012Metric
FB8, FB9, FB10: 600@100Mhz; R_0603_1608Metric
R30, R31, R32: 4.7; R_0603_1608Metric
U18, U19, U20: SN74LVC3G04; MSOP-8_3x3mm_P0.65mm

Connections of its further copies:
/T-OscilatorRing1/R_PAD2: U18.1; also elsewhere on the board
/T-OscilatorRing2/R_PAD2: U19.1; also elsewhere on the board
/TD2: U18.5; also elsewhere on the board
/TD3: U19.5; also elsewhere on the board
/TD4: U20.1, U20.5; also elsewhere on the board
GND: C36.2, C37.2, C38.2, C39.2, C40.2, C41.2, C57.2, C59.2, C60.2, U18.4 (GND), U19.4 (GND), U20.4 (GND); also elsewhere on the board
unnamed: FB8.1, R30.1
unnamed: FB9.1, R31.1
unnamed: FB10.1, R32.1
unnamed: U18.2, U18.3
unnamed: U18.6, U18.7
unnamed: C36.1, C37.1, C57.1, R30.2, U18.8 (VCC)
unnamed: U19.2, U19.3
unnamed: U19.6, U19.7
unnamed: C38.1, C39.1, C59.1, R31.2, U19.8 (VCC)
unnamed: U20.2, U20.3
unnamed: U20.6, U20.7
unnamed: C40.1, C41.1, C60.1, R32.2, U20.8 (VCC)
VDDA: FB8.2, FB9.2, FB10.2; also elsewhere on the board

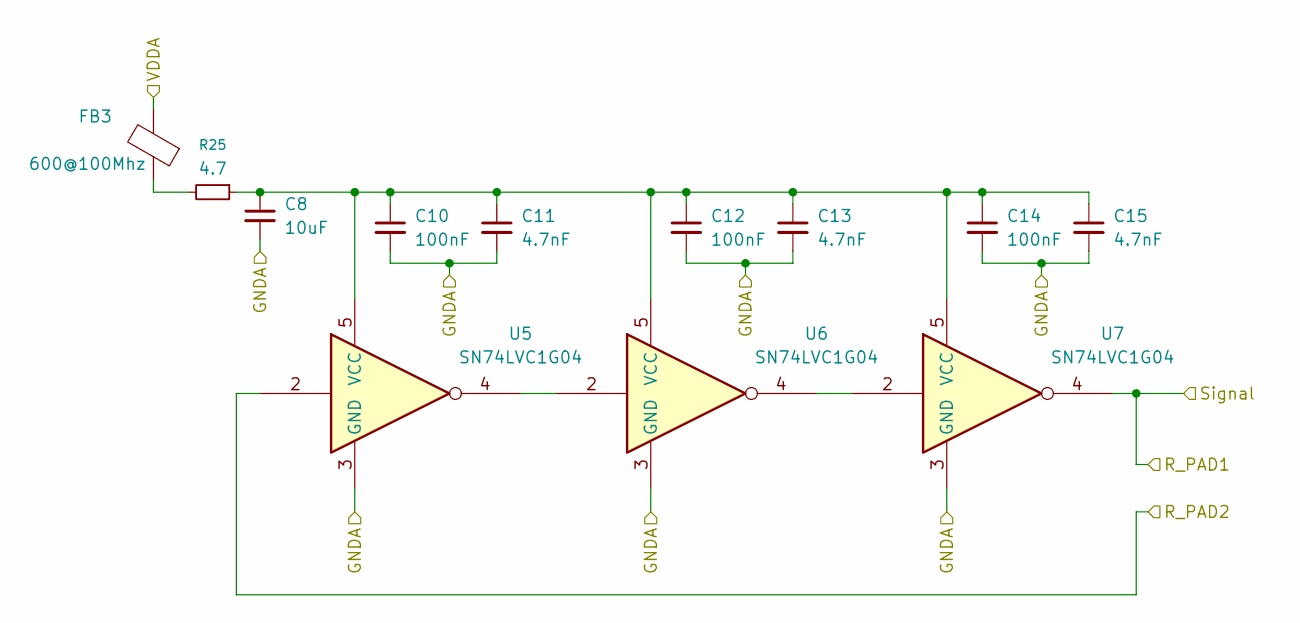
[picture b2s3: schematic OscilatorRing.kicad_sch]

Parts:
C8: 10uF; C_0805_2012Metric
C10, C12, C14: 100nF; C_0402_1005Metric
C11, C13, C15: 4.7nF; C_0402_1005Metric
FB3: 600@100Mhz; R_0603_1608Metric
R25: 4.7; R_0603_1608Metric
U5, U6, U7: SN74LVC1G04; SOT-353_SC-70-5

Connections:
/D1: U7.4; also elsewhere on the board
/OscilatorRing1/R_PAD2: U5.2; also elsewhere on the board
GND: C8.2, C10.2, C11.2, C12.2, C13.2, C14.2, C15.2, U5.3 (GND), U6.3 (GND), U7.3 (GND); also elsewhere on the board
unnamed: FB3.1, R25.2
unnamed: U5.4, U6.2
unnamed: C8.1, C10.1, C11.1, C12.1, C13.1, C14.1, C15.1, R25.1, U5.5 (VCC), U6.5 (VCC), U7.5 (VCC)
unnamed: U6.4, U7.2
VDDA: FB3.2; also elsewhere on the board

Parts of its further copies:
C9, C44, C45: 10uF; C_0805_2012Metric
C16, C18, C20, C22, C24, C26, C28, C30, C32: 100nF; C_0402_1005Metric
C17, C19, C21, C23, C25, C27, C29, C31, C33: 4.7nF; C_0402_1005Metric
FB4, FB5, FB6: 600@100Mhz; R_0603_1608Metric
R26, R27, R28: 4.7; R_0603_1608Metric
U8, U9, U10, U11, U12, U13, U14, U15, U16: SN74LVC1G04; SOT-353_SC-70-5

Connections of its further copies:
/D2: U10.4; also elsewhere on the board
/D3: U13.4; also elsewhere on the board
/D4: U16.4; also elsewhere on the board
/OscilatorRing2/R_PAD2: U8.2; also elsewhere on the board
/OscilatorRing3/R_PAD2: U11.2; also elsewhere on the board
/OscilatorRing4/R_PAD2: U14.2; also elsewhere on the board
GND: C9.2, C16.2, C17.2, C18.2, C19.2, C20.2, C21.2, C22.2, C23.2, C24.2, C25.2, C26.2, C27.2, C28.2, C29.2, C30.2, C31.2, C32.2, C33.2, C44.2, C45.2, U8.3 (GND), U9.3 (GND), U10.3 (GND), U11.3 (GND), U12.3 (GND), U13.3 (GND), U14.3 (GND), U15.3 (GND), U16.3 (GND); also elsewhere on the board
unnamed: FB4.1, R26.2
unnamed: FB5.1, R27.2
unnamed: FB6.1, R28.2
unnamed: U8.4, U9.2
unnamed: U9.4, U10.2
unnamed: C9.1, C16.1, C17.1, C18.1, C19.1, C20.1, C21.1, R26.1, U8.5 (VCC), U9.5 (VCC), U10.5 (VCC)
unnamed: U11.4, U12.2
unnamed: C22.1, C23.1, C24.1, C25.1, C26.1, C27.1, C44.1, R27.1, U11.5 (VCC), U12.5 (VCC), U13.5 (VCC)
unnamed: U12.4, U13.2
unnamed: U14.4, U15.2
unnamed: C28.1, C29.1, C30.1, C31.1, C32.1, C33.1, C45.1, R28.1, U14.5 (VCC), U15.5 (VCC), U16.5 (VCC)
unnamed: U15.4, U16.2
VDDA: FB4.2, FB5.2, FB6.2; also elsewhere on the board
